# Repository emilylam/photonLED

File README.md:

# photonLED

Breakout board for MC-E LED for the Photon.

Repository includes some barebones example code.

LED wiring: <br>
white -- A5 <br>
red -- A4 <br>
green -- WKP <br>
blue -- TX <br>

There is also a color sensor, TCS34725. It's wired up to the I2C bus. Just use the Adafruit library.

Power: <br>
5V on USB, 5V on terminal block, or 7-12V on DC jack. Total current consumption is around 900mA. Make sure power source can source 1A.

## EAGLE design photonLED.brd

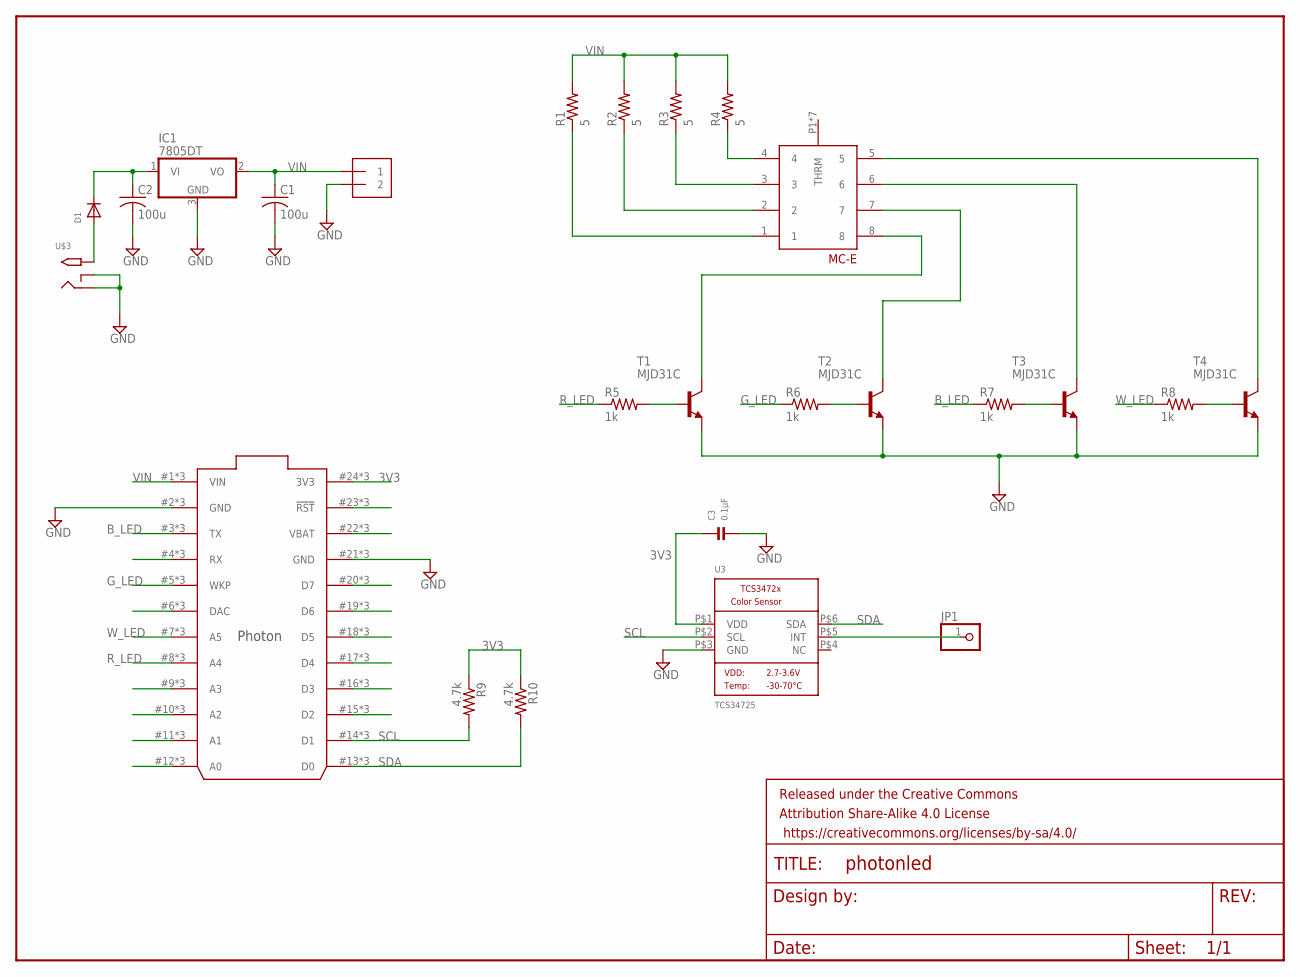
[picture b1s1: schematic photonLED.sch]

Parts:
C1, C2: 100u; C0805
C3: 0.1µF; _0805
D1: DIODESOD-123; SOD-123
FRAME1: FRAME-LETTER; CREATIVE_COMMONS
IC1: 7805DT; TO252
J1: 3.5MM Screw Term; 1X2-3.5MM
JP1: PINHD-1X1; 1X01
R1, R2, R3, R4: 5; R2512
R5, R6, R7, R8: 1k; R0805
R9, R10: 4.7k; R0805
T1, T2, T3, T4: MJD31C; DPAK
U3: TCS34725; TCS3472_FN6
U$1: PHOTON_WITH_STACKABLE_HEADERS; PHOTON_STACKABLE
U$2: MC-E
U$3: 2.1MMJACKSMT; DCJACK_2MM_SMT

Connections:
3V3: C3.1, R9.1, R10.1, U3.P$1 (VDD), U$1.24 (3V3), U$1.#24 (3V3), U$1.@24 (3V3)
B_LED: R7.1, U$1.3 (TX), U$1.#3 (TX), U$1.@3 (TX)
GND: C1.2, C2.2, C3.2, IC1.3 (GND), J1.2, T1.3 (E), T2.3 (E), T3.3 (E), T4.3 (E), U3.P$3 (GND), U$1.2 (GND), U$1.21 (GND), U$1.#2 (GND), U$1.#21 (GND), U$1.@2 (GND), U$1.@21 (GND), U$3.GND (RING), U$3.GNDBREAK (RING_SW)
G_LED: R6.1, U$1.5 (WKP), U$1.#5 (WKP), U$1.@5 (WKP)
unnamed: R4.1, U$2.4
unnamed: R3.1, U$2.3
unnamed: R2.1, U$2.2
unnamed: R1.1, U$2.1
unnamed: T1.4 (C), U$2.8
unnamed: R6.2, T2.1 (B)
unnamed: T2.4 (C), U$2.7
unnamed: T3.4 (C), U$2.6
unnamed: D1.A, U$3.PWR2 (TIP)
unnamed: C2.1, D1.C, IC1.1 (VI)
unnamed: JP1.1, U3.P$5 (INT)
unnamed: U$1.10 (A2), U$1.#10 (A2), U$1.@10 (A2)
unnamed: U$1.6 (DAC), U$1.#6 (DAC), U$1.@6 (DAC)
unnamed: U$1.4 (RX), U$1.#4 (RX), U$1.@4 (RX)
unnamed: U$1.9 (A3), U$1.#9 (A3), U$1.@9 (A3)
unnamed: T4.4 (C), U$2.5
unnamed: U$1.11 (A1), U$1.#11 (A1), U$1.@11 (A1)
unnamed: U$1.12 (A0), U$1.#12 (A0), U$1.@12 (A0)
unnamed: U$1.23 (!RST), U$1.#23 (!RST), U$1.@23 (!RST)
unnamed: U$1.22 (VBAT), U$1.#22 (VBAT), U$1.@22 (VBAT)
unnamed: U$1.20 (D7), U$1.#20 (D7), U$1.@20 (D7)
unnamed: U$1.19 (D6), U$1.#19 (D6), U$1.@19 (D6)
unnamed: U$1.18 (D5), U$1.#18 (D5), U$1.@18 (D5)
unnamed: U$1.17 (D4), U$1.#17 (D4), U$1.@17 (D4)
unnamed: U$1.16 (D3), U$1.#16 (D3), U$1.@16 (D3)
unnamed: U$1.15 (D2), U$1.#15 (D2), U$1.@15 (D2)
unnamed: R5.2, T1.1 (B)
unnamed: R7.2, T3.1 (B)
unnamed: R8.2, T4.1 (B)
R_LED: R5.1, U$1.8 (A4), U$1.#8 (A4), U$1.@8 (A4)
SCL: R9.2, U3.P$2 (SCL), U$1.14 (D1), U$1.#14 (D1), U$1.@14 (D1)
SDA: R10.2, U3.P$6 (SDA), U$1.13 (D0), U$1.#13 (D0), U$1.@13 (D0)
VIN: C1.1, IC1.2 (VO), J1.1, R1.2, R2.2, R3.2, R4.2, U$1.1 (VIN), U$1.#1 (VIN), U$1.@1 (VIN)
W_LED: R8.1, U$1.7 (A5), U$1.#7 (A5), U$1.@7 (A5)

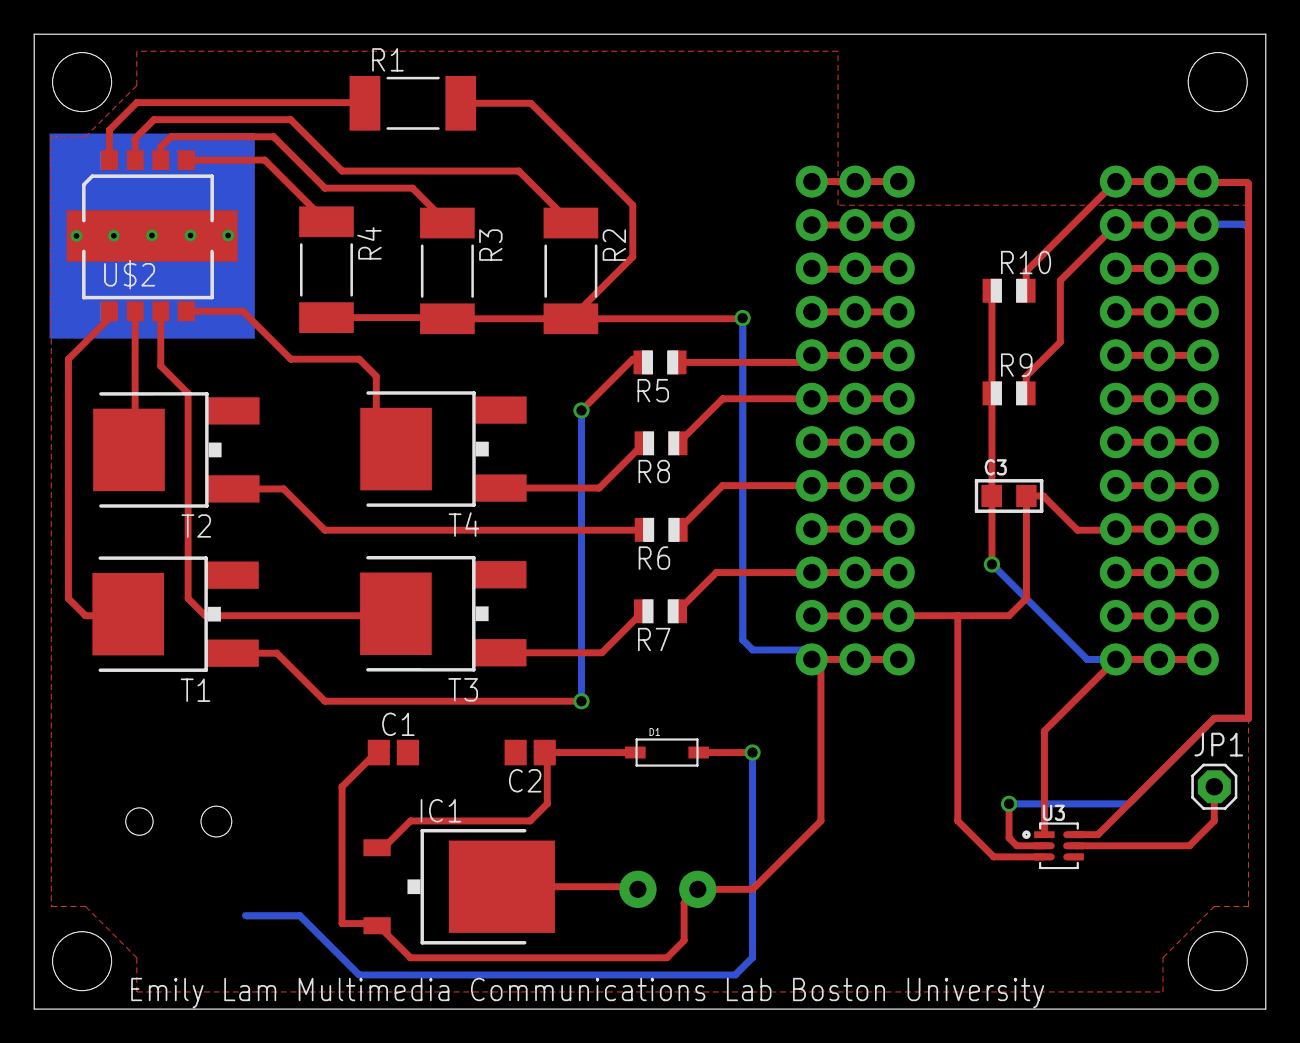
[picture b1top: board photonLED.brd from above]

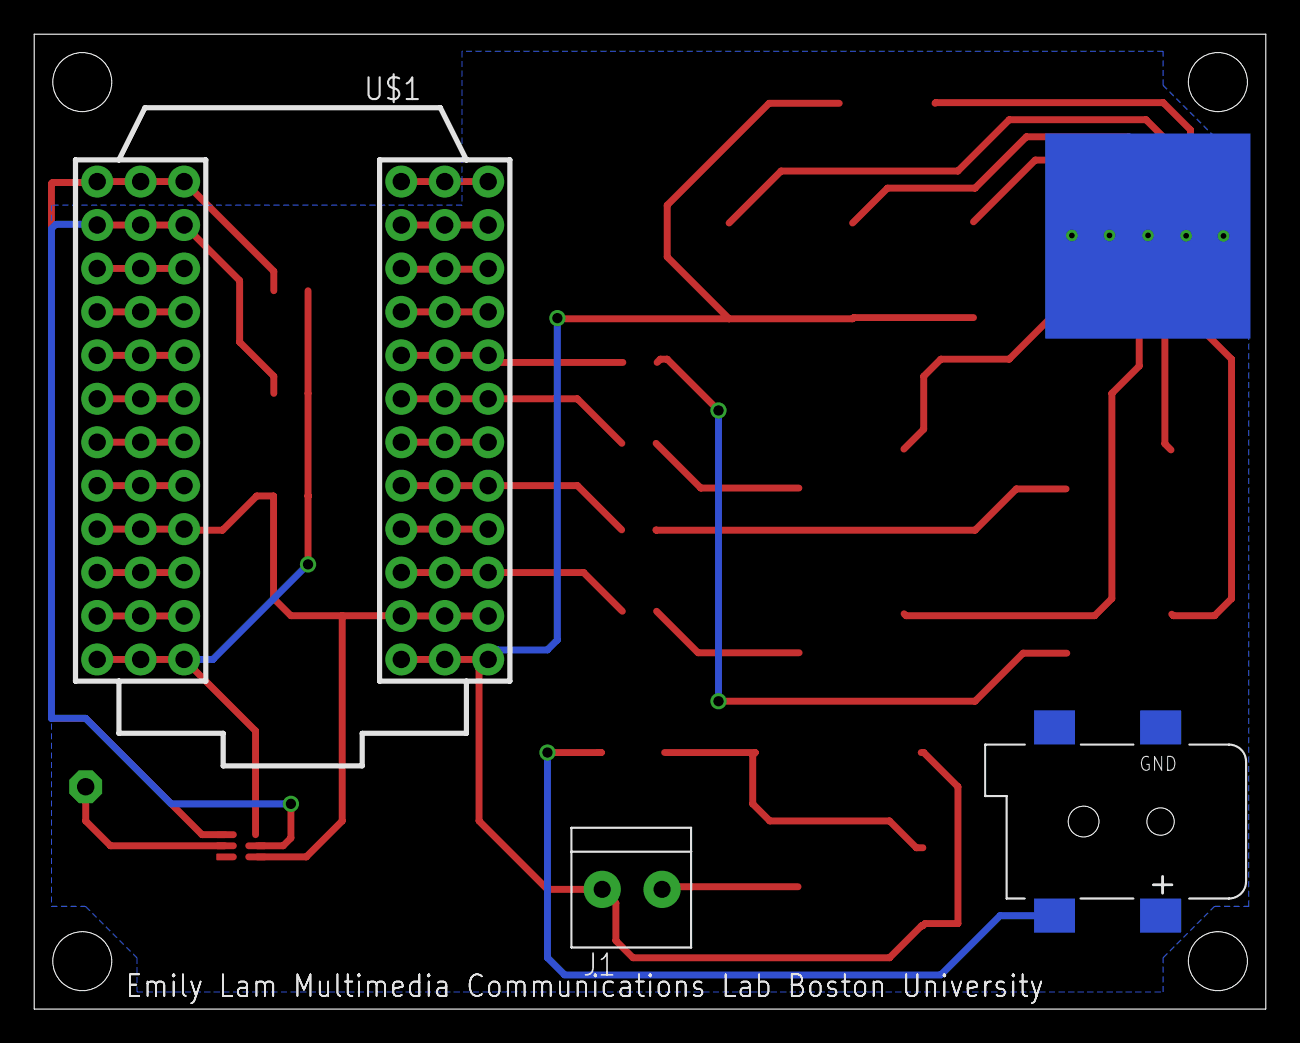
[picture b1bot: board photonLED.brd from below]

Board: 2 copper layers, 72.0 x 57.0 mm, 26 parts (3 on the bottom side), 38 nets.

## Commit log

2016-10-24 draft broad
2016-10-24 added voltage regulator, DC terminals, all on one side.
2016-10-26 added color sensor, mounting holes, ground planes, etc.
2016-10-28 final board layout
2016-12-16 final board
2016-12-16 removed test.html

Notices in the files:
parts and their libraries:
SparkFun-Aesthetics: Licensing: Creative Commons ShareAlike 4.0 International - https://creativecommons.org/licenses/by-sa/4.0
SparkFun-Aesthetics: Released under the Creative Commons Attribution Share-Alike 4.0 License
SparkFun-Aesthetics: https://creativecommons.org/licenses/by-sa/4.0
